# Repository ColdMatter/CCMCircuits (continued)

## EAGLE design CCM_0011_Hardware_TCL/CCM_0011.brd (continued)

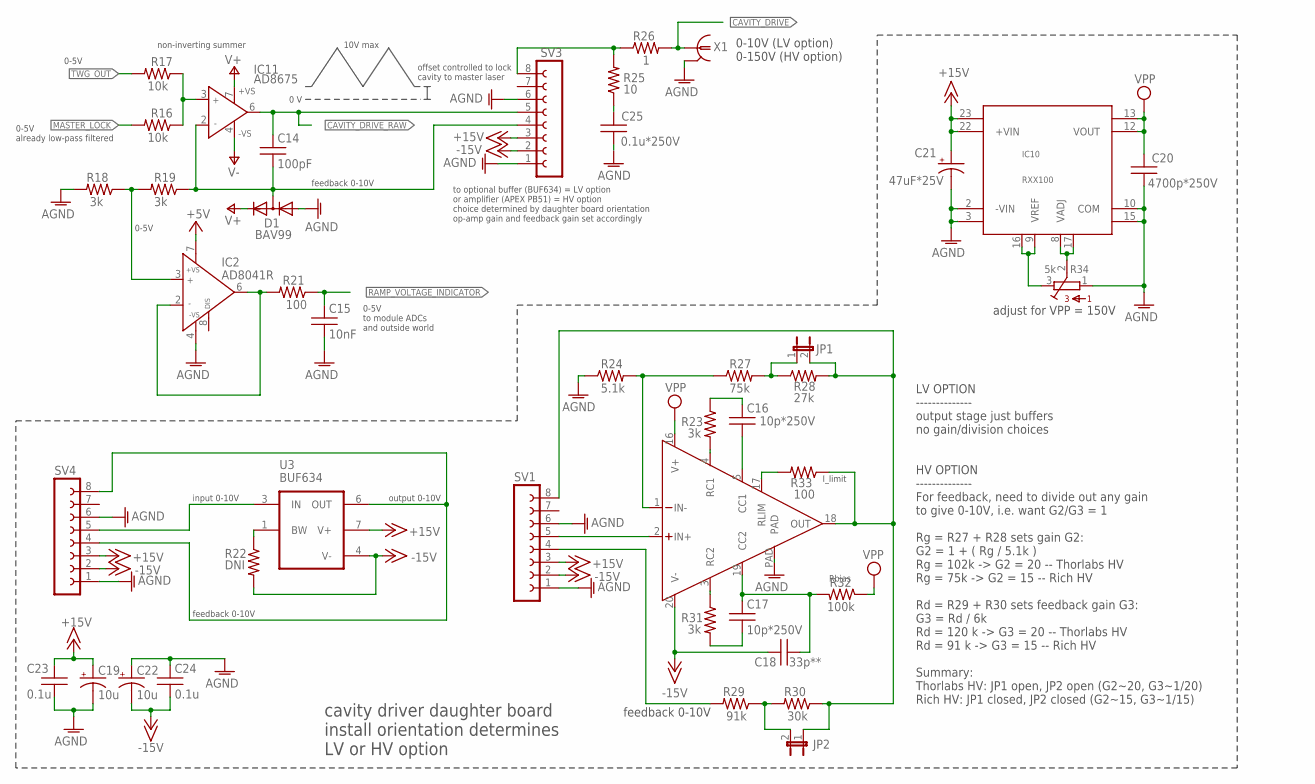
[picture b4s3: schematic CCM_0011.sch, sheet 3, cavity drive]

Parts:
C14: 100pF; 0603
C15: 10nF; 0603
C16, C17: 10p*250V; 0603
C18: 33p**; 0603
C19, C22: 10u; EIA3216
C20: 4700p*250V; 1210
C21: 47uF*25V; EIA7343
C23, C24: 0.1u; 0603
C25: 0.1u*250V; 1210
D1: BAV99; SOT23
IC2: AD8041R; SO8
IC10: RXX100; RXXDIP
IC11: AD8675; SO08
JP1, JP2: JP1E; JP1
R16, R17: 10k; 0603
R18, R19, R23, R31: 3k; 0603
R21, R33: 100; 0603
R22: DNI; 0603
R24: 5.1k; 0603
R25: 10; 2512
R26: 1; 2512
R27: 75k; 0603
R28: 27k; 0603
R29: 91k; 0603
R30: 30k; 0603
R32: 100k; 0603
R34: 5k; 3386H
SV1, SV4: FE08W
SV3: FE08-1; FE08
U3: BUF634; SO8
U$1: PA78; PSOP-20
X1: 1-227161-0; AMP_227161

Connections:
+5V: IC2.7 (+VS); also elsewhere on the board
+15V: C19.A (+), C21.A (+), C23.1, IC10.22 (+VIN), IC10.23 (VIN2+), SV1.3, SV3.3, SV4.3, U3.7 (V+)
-15V: C18.2, C22.C (-), C24.2, R22.2, SV1.2, SV3.2, SV4.2, U3.4 (V-), U$1.20 (V-)
AGND: C15.2, C19.C (-), C20.2, C21.C (-), C22.A (+), C23.2, C24.1, C25.2, D1.1 (A), IC2.4 (-VS), IC10.2 (-VIN), IC10.3 (VIN2-), IC10.10 (COM), IC10.15 (COM2), R18.2, R24.1, R34.1, SV1.1, SV1.6, SV3.1, SV3.6, SV4.1, SV4.6, U$1.PAD, X1.2; also elsewhere on the board
CAVITY_DRIVE: R26.2, X1.1
CAVITY_DRIVE_RAW: C14.1, IC11.6 (OUT), SV3.5
MASTER_LOCK: R16.2
unnamed: SV4.5, U3.3 (IN)
unnamed: IC2.3 (IN+), R18.1, R19.2
unnamed: JP2.2, R29.1, R30.2
unnamed: C14.2, D1.3 (AC), IC11.2 (IN-), R19.1, SV3.4
unnamed: IC11.3 (IN+), R16.1, R17.1
unnamed: R22.1, U3.1 (BW)
unnamed: SV4.4, SV4.8, U3.6 (OUT)
unnamed: SV1.5, U$1.2 (IN+)
unnamed: IC2.2 (IN-), IC2.6 (OUT), R21.2
unnamed: C16.1, R23.1
unnamed: JP1.2, JP2.1, R28.2, R30.1, R33.1, SV1.8, U$1.18 (OUT)
unnamed: R25.2, R26.1, SV3.8
unnamed: C25.1, R25.1
unnamed: R33.2, U$1.17 (RLIM)
unnamed: JP1.1, R27.2, R28.1
unnamed: R23.2, U$1.4 (RC1)
unnamed: R24.2, R27.1, U$1.1 (IN-)
unnamed: C16.2, U$1.5 (CC1)
unnamed: R29.2, SV1.4
unnamed: R31.1, U$1.3 (RC2)
unnamed: C17.1, C18.1, R32.2, U$1.19 (CC2)
unnamed: C17.2, R31.2
unnamed: IC10.9 (VREF), IC10.16 (VREF2), R34.3
unnamed: IC10.8 (VADJ), IC10.17 (VADJ2), R34.2
RAMP_VOLTAGE_INDICATOR: C15.1, R21.1
TWG_OUT: R17.2; also elsewhere on the board
V+: D1.2 (C), IC11.7 (+VS); also elsewhere on the board
V-: IC11.4 (-VS); also elsewhere on the board
VOUT2: C20.1, IC10.12 (VOUT), IC10.13 (VOUT2)
VPP: R32.1, U$1.16 (V+)

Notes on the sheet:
0-5V already low-pass filtered
0-5V
0 V
10V max
offset controlled to lock cavity to master laser
non-inverting summer
feedback 0-10V
0-5V to module ADCs and outside world
to optional buffer (BUF634) = LV option or amplifier (APEX PB51) = HV option choice determined by daughter board orientation op-amp gain and feedback gain set accordingly
output 0-10V
input 0-10V
cavity driver daughter board install orientation determines LV or HV option
LV OPTION -------------- output stage just buffers no gain/division choices HV OPTION -------------- For feedback, need to divide out any gain to give 0-10V, i.e. want G2/G3 = 1 Rg = R27 + R28 sets gain G2: G2 = 1 + ( Rg / 5.1k ) Rg = 102k -> G2 = 20 -- Thorlabs HV Rg = 75k -> G2 = 15 -- Rich HV Rd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
0-10V (LV option) 0-150V (HV option)
Rbias
I_limit
adjust for VPP = 150V

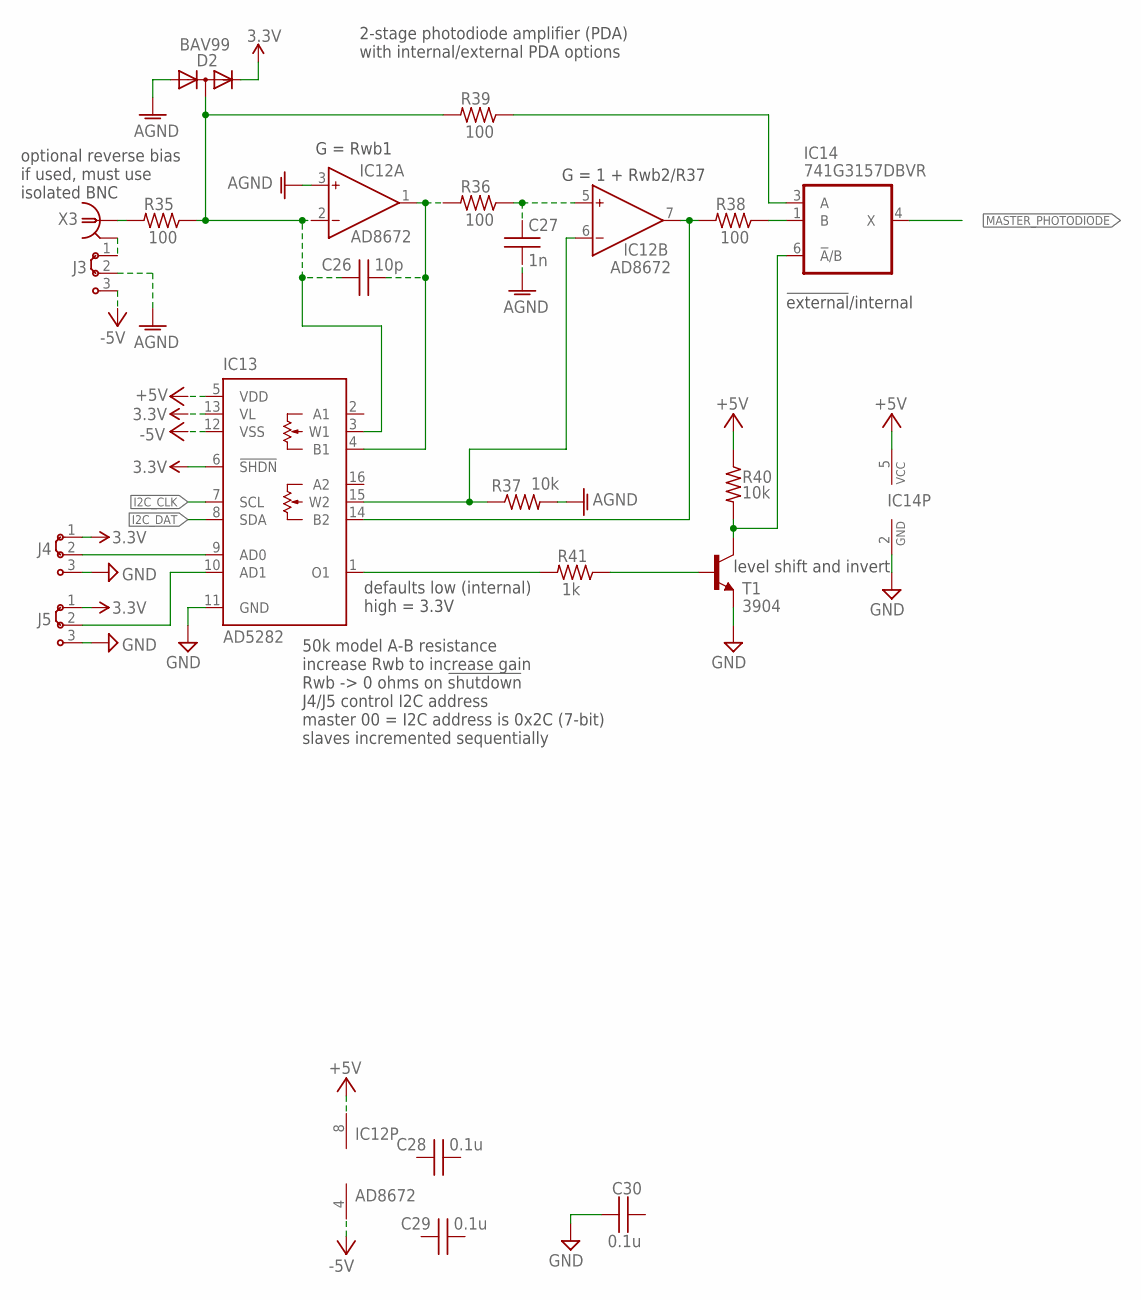
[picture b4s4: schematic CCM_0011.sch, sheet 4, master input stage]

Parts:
C26: 10p; 0603
C27: 1n; 0603
C28, C29, C30: 0.1u; 0603
D2: BAV99; SOT23
IC12: AD8672; SO8
IC13: AD5282; TSSOP16
IC14: 741G3157DBVR; DBV_R-PDSO-G6
J3, J4, J5: J2X2MM; 04C
R35, R36, R38, R39: 100; 0603
R37, R40: 10k; 0603
R41: 1k; 0603
T1: 3904; SOT23-BEC
X3: 1-227161-0; AMP_227161

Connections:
3.3V: D2.2 (C), IC13.6 (!SHDN), IC13.13 (VL), J4.1, J5.1; also elsewhere on the board
+5V: IC12.8 (V+), IC13.5 (VDD), IC14.5 (VCC), R40.1; also elsewhere on the board
-5V: IC12.4 (V-), IC13.12 (VSS), J3.3
AGND: C27.2, D2.1 (A), IC12.3 (IN+), J3.2, R37.2; also elsewhere on the board
GND: C30.2, IC13.11 (GND), IC14.2 (GND), J4.3, J5.3, T1.E; also elsewhere on the board
I2C_CLK: IC13.7 (SCL)
I2C_DAT: IC13.8 (SDA)
MASTER_PHOTODIODE: IC14.4 (X)
unnamed: IC12.7 (OUT), IC13.14 (B2), R38.2
unnamed: J3.1, X3.2
unnamed: C26.1, D2.3 (AC), IC12.2 (IN-), IC13.3 (W1), R35.1, R39.2
unnamed: IC12.6 (IN-), IC13.15 (W2), R37.1
unnamed: R41.1, T1.B
unnamed: IC14.1 (B), R38.1
unnamed: C27.1, IC12.5 (IN+), R36.1
unnamed: C26.2, IC12.1 (OUT), IC13.4 (B1), R36.2
unnamed: IC14.3 (A), R39.1
unnamed: IC14.6 (!A!/B), R40.2, T1.C
unnamed: IC13.1 (O1), R41.2
unnamed: R35.2, X3.1
unnamed: IC13.10 (AD1), J5.2
unnamed: IC13.9 (AD0), J4.2

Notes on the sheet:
optional reverse bias if used, must use isolated BNC
2-stage photodiode amplifier (PDA) with internal/external PDA options
50k model A-B resistance increase Rwb to increase gain Rwb -> 0 ohms on !shutdown! J4/J5 control I2C address master 00 = I2C address is 0x2C (7-bit) slaves incremented sequentially
!external!/internal
defaults low (internal) high = 3.3V
level shift and invert
G = 1 + Rwb2/R37
G = Rwb1

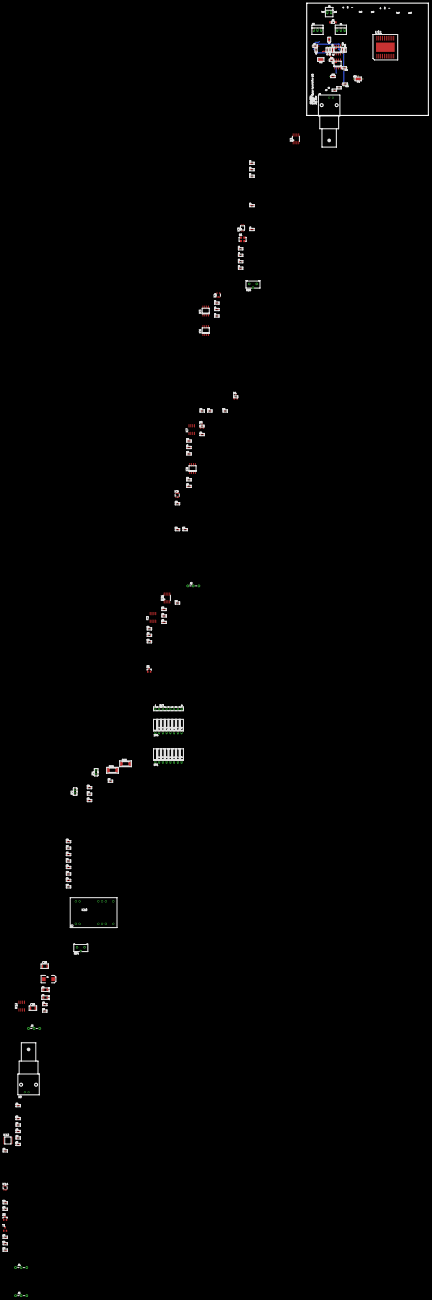
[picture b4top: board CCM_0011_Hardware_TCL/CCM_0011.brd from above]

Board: 2 copper layers, 82.5 x 76.2 mm, 120 parts (0 on the bottom side), 73 nets.

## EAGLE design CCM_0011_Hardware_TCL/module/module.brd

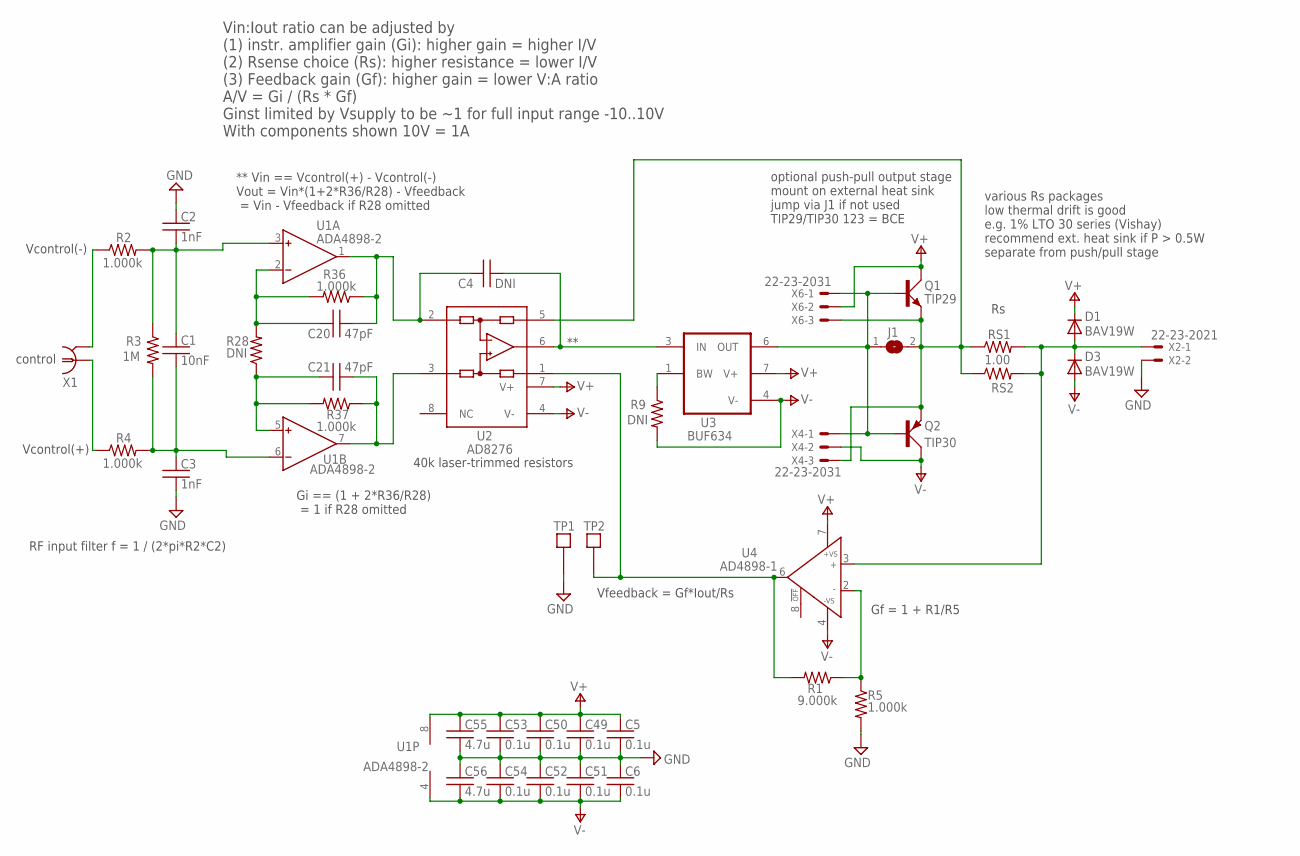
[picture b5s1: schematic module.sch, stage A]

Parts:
C1: 10nF; 0603
C2, C3: 1nF; 0603
C4: DNI; 0603
C5, C6, C49, C50, C51, C52, C53, C54: 0.1u; 0603
C20, C21: 47pF; 0603
C55, C56: 4.7u; 0603
D1, D3: BAV19W; SOD123
J1: SJ
Q1: TIP29; TO220AV
Q2: TIP30; TO220AV
R1: 9.000k; 0603
R2, R4, R5, R36, R37: 1.000k; 0603
R3: 1M; 0603
R9, R28: DNI; 0603
RS1: 1.00; LTO30
RS2: DNI; 2512
TP1, TP2: TESTPOINT
U1: ADA4898-2; SO8
U2: AD8276; SO8
U3: BUF634; SO8
U4: AD4898-1; SO8
X1: 1-227161-0; AMP_227161
X2: 22-23-2021
X4, X6: 22-23-2031

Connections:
GND: C2.1, C3.2, C5.2, C6.1, C49.2, C50.2, C51.1, C52.1, C53.2, C54.1, C55.2, C56.1, R5.2, TP1.P$1, X2.2
unnamed: R2.1, X1.2
unnamed: R4.1, X1.1
unnamed: C4.2, U2.6 (OUT), U3.3 (IN)
unnamed: C1.1, C2.2, R2.2, R3.1, U1.3 (IN+)
unnamed: C1.2, C3.1, R3.2, R4.2, U1.6 (IN-)
unnamed: R1.1, R5.1, U4.2 (IN-)
unnamed: J1.1, Q1.B, Q2.B, U3.6 (OUT), X4.1, X6.1
unnamed: D1.A, D3.C, RS1.P$2 (2), RS2.2, U4.3 (IN+), X2.1
unnamed: J1.2, Q1.E, Q2.E, RS1.P$1 (1), RS2.1, U2.5 (SENSE), X4.3, X6.3
unnamed: R9.1, U3.1 (BW)
unnamed: R1.2, TP2.P$1, U2.1 (REF), U4.6 (OUT)
unnamed: C20.1, R28.2, R36.2, U1.2 (IN-)
unnamed: C21.1, R28.1, R37.2, U1.5 (IN+)
unnamed: C21.2, R37.1, U1.7 (OUT), U2.3 (+IN)
unnamed: C4.1, C20.2, R36.1, U1.1 (OUT), U2.2 (-IN)
V+: C5.1, C49.1, C50.1, C53.1, C55.1, D1.C, Q1.C, U1.8 (V+), U2.7 (V+), U3.7 (V+), U4.7 (+VS), X6.2
V-: C6.2, C51.2, C52.2, C54.2, C56.2, D3.A, Q2.C, R9.2, U1.4 (V-), U2.4 (V-), U3.4 (V-), U4.4 (-VS), X4.2

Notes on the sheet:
control
RF input filter f = 1 / (2*pi*R2*C2)
optional push-pull output stage mount on external heat sink jump via J1 if not used TIP29/TIP30 123 = BCE
40k laser-trimmed resistors
Vcontrol(+)
Vcontrol(-)
various Rs packages low thermal drift is good e.g. 1% LTO 30 series (Vishay) recommend ext. heat sink if P > 0.5W separate from push/pull stage
** Vin == Vcontrol(+) - Vcontrol(-) Vout = Vin*(1+2*R36/R28) - Vfeedback = Vin - Vfeedback if R28 omitted
Gi == (1 + 2*R36/R28) = 1 if R28 omitted
Vfeedback = Gf*Iout/Rs
Gf = 1 + R1/R5
Vin:Iout ratio can be adjusted by (1) instr. amplifier gain (Gi): higher gain = higher I/V (2) Rsense choice (Rs): higher resistance = lower I/V (3) Feedback gain (Gf): higher gain = lower V:A ratio A/V = Gi / (Rs * Gf) Ginst limited by Vsupply to be ~1 for full input range -10..10V With components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

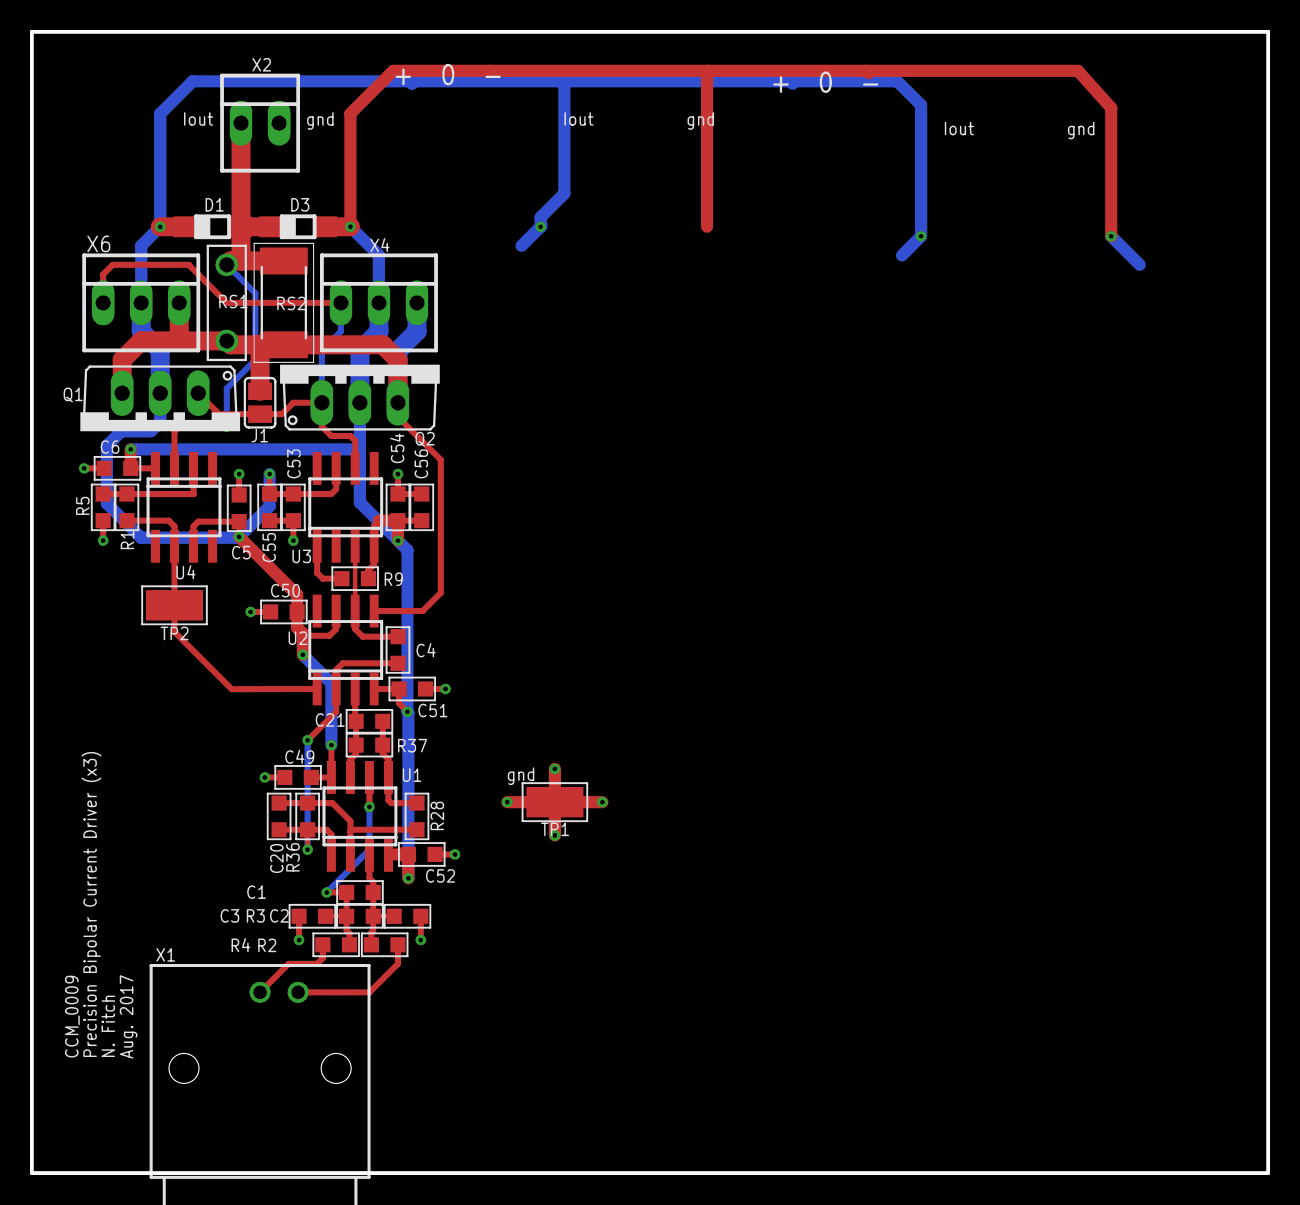
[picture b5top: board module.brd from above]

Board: 2 copper layers, 82.5 x 76.2 mm, 42 parts (0 on the bottom side), 18 nets.

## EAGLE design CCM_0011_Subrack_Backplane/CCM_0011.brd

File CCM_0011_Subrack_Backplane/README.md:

Subrack Backplane
===========
     
This circuit is an attempt to create a subrack standard for CCM circuits.  It uses a 64-pin bus based on the EURO-card standard (100 mm tall boards x various lengths, typically 160 mm) using DIN41612 "Type B" connectors.  The bus provides separate analog and digital ground planes and associated power supplies of +/-15V and +/-5V, respectively.  The backplane provides female connectors with a 4HP pitch.

We have a number of existing circuits that use a 32-pin rear connector (actually a 64-pin connector with half of the pins unpopulated).  The bus standard defined here should be compatible with our existing circuits.

In addition to power rails, the backplane also provides various communication buses, which can be used with microcontroller projects.  Take care though, the GPIOX and ANX lines are shared across all daughter boards, which can cause conflicts if you aren't careful.  In a similar vein, please only install a single power-supply module!

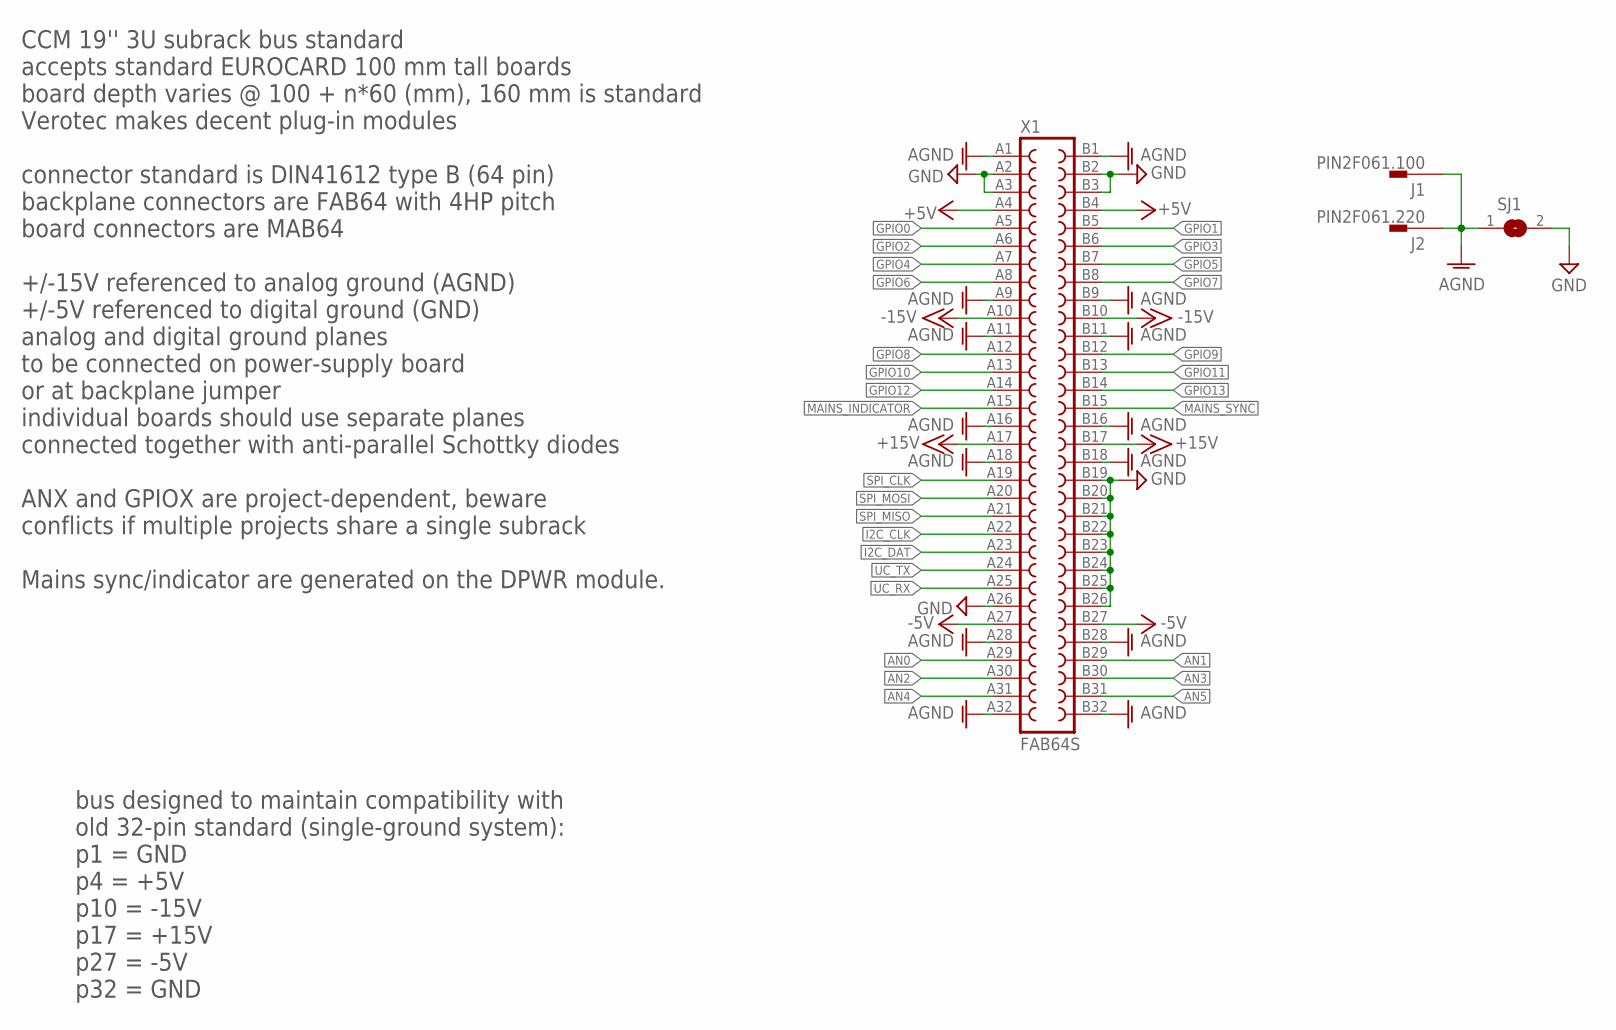
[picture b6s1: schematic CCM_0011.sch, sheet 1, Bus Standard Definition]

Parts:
J1: PIN2F061.100; F061.100
J2: PIN2F061.220; F061.220
SJ1: SJ
X1: FAB64S

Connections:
+5V: X1.A4, X1.B4; also elsewhere on the board
+15V: X1.A17, X1.B17; also elsewhere on the board
-5V: X1.A27, X1.B27; also elsewhere on the board
-15V: X1.A10, X1.B10; also elsewhere on the board
AGND: J1.A1, J1.A2, J2.1A, J2.1B, SJ1.1, X1.A1, X1.A9, X1.A11, X1.A16, X1.A18, X1.A28, X1.A32, X1.B1, X1.B9, X1.B11, X1.B16, X1.B18, X1.B28, X1.B32; also elsewhere on the board
AN0: X1.A29; also elsewhere on the board
AN1: X1.B29; also elsewhere on the board
AN2: X1.A30; also elsewhere on the board
AN3: X1.B30; also elsewhere on the board
AN4: X1.A31; also elsewhere on the board
AN5: X1.B31; also elsewhere on the board
GND: SJ1.2, X1.A2, X1.A3, X1.A26, X1.B2, X1.B3, X1.B19, X1.B20, X1.B21, X1.B22, X1.B23, X1.B24, X1.B25, X1.B26; also elsewhere on the board
GPIO0: X1.A5; also elsewhere on the board
GPIO1: X1.B5; also elsewhere on the board
GPIO2: X1.A6; also elsewhere on the board
GPIO3: X1.B6; also elsewhere on the board
GPIO4: X1.A7; also elsewhere on the board
GPIO5: X1.B7; also elsewhere on the board
GPIO6: X1.A8; also elsewhere on the board
GPIO7: X1.B8; also elsewhere on the board
GPIO8: X1.A12; also elsewhere on the board
GPIO9: X1.B12; also elsewhere on the board
GPIO10: X1.A13; also elsewhere on the board
GPIO11: X1.B13; also elsewhere on the board
GPIO12: X1.A14; also elsewhere on the board
GPIO13: X1.B14; also elsewhere on the board
I2C_CLK: X1.A22; also elsewhere on the board
I2C_DAT: X1.A23; also elsewhere on the board
MAINS_INDICATOR: X1.A15
MAINS_SYNC: X1.B15
SPI_CLK: X1.A19; also elsewhere on the board
SPI_MISO: X1.A21; also elsewhere on the board
SPI_MOSI: X1.A20; also elsewhere on the board
UC_RX: X1.A25; also elsewhere on the board
UC_TX: X1.A24; also elsewhere on the board

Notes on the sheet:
bus designed to maintain compatibility with old 32-pin standard (single-ground system): p1 = GND p4 = +5V p10 = -15V p17 = +15V p27 = -5V p32 = GND
CCM 19'' 3U subrack bus standard accepts standard EUROCARD 100 mm tall boards board depth varies @ 100 + n*60 (mm), 160 mm is standard Verotec makes decent plug-in modules connector standard is DIN41612 type B (64 pin) backplane connectors are FAB64 with 4HP pitch board connectors are MAB64 +/-15V 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

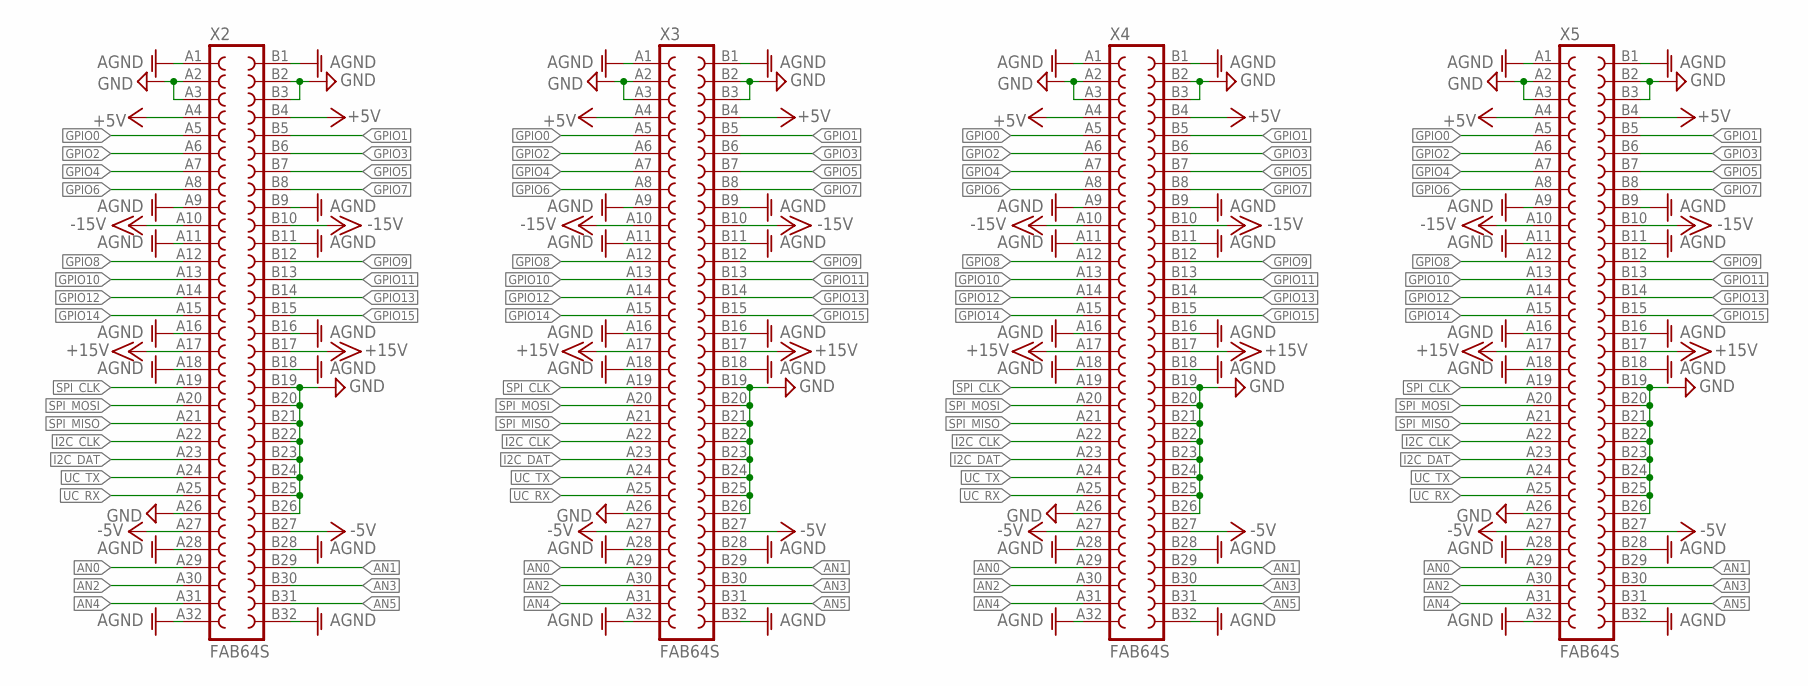
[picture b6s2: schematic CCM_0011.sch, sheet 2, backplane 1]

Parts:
X2, X3, X4, X5: FAB64S

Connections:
+5V: X2.A4, X2.B4, X3.A4, X3.B4, X4.A4, X4.B4, X5.A4, X5.B4; also elsewhere on the board
+15V: X2.A17, X2.B17, X3.A17, X3.B17, X4.A17, X4.B17, X5.A17, X5.B17; also elsewhere on the board
-5V: X2.A27, X2.B27, X3.A27, X3.B27, X4.A27, X4.B27, X5.A27, X5.B27; also elsewhere on the board
-15V: X2.A10, X2.B10, X3.A10, X3.B10, X4.A10, X4.B10, X5.A10, X5.B10; also elsewhere on the board
AGND: X2.A1, X2.A9, X2.A11, X2.A16, X2.A18, X2.A28, X2.A32, X2.B1, X2.B9, X2.B11, X2.B16, X2.B18, X2.B28, X2.B32, X3.A1, X3.A9, X3.A11, X3.A16, X3.A18, X3.A28, X3.A32, X3.B1, X3.B9, X3.B11, X3.B16, X3.B18, X3.B28, X3.B32, X4.A1, X4.A9, X4.A11, X4.A16, X4.A18, X4.A28, X4.A32, X4.B1, X4.B9, X4.B11, X4.B16, X4.B18, X4.B28, X4.B32, X5.A1, X5.A9, X5.A11, X5.A16, X5.A18, X5.A28, X5.A32, X5.B1, X5.B9, X5.B11, X5.B16, X5.B18, X5.B28, X5.B32; also elsewhere on the board
AN0: X2.A29, X3.A29, X4.A29, X5.A29; also elsewhere on the board
AN1: X2.B29, X3.B29, X4.B29, X5.B29; also elsewhere on the board
AN2: X2.A30, X3.A30, X4.A30, X5.A30; also elsewhere on the board
AN3: X2.B30, X3.B30, X4.B30, X5.B30; also elsewhere on the board
AN4: X2.A31, X3.A31, X4.A31, X5.A31; also elsewhere on the board
AN5: X2.B31, X3.B31, X4.B31, X5.B31; also elsewhere on the board
GND: X2.A2, X2.A3, X2.A26, X2.B2, X2.B3, X2.B19, X2.B20, X2.B21, X2.B22, X2.B23, X2.B24, X2.B25, X2.B26, X3.A2, X3.A3, X3.A26, X3.B2, X3.B3, X3.B19, X3.B20, X3.B21, X3.B22, X3.B23, X3.B24, X3.B25, X3.B26, X4.A2, X4.A3, X4.A26, X4.B2, X4.B3, X4.B19, X4.B20, X4.B21, X4.B22, X4.B23, X4.B24, X4.B25, X4.B26, X5.A2, X5.A3, X5.A26, X5.B2, X5.B3, X5.B19, X5.B20, X5.B21, X5.B22, X5.B23, X5.B24, X5.B25, X5.B26; also elsewhere on the board
GPIO0: X2.A5, X3.A5, X4.A5, X5.A5; also elsewhere on the board
GPIO1: X2.B5, X3.B5, X4.B5, X5.B5; also elsewhere on the board
GPIO2: X2.A6, X3.A6, X4.A6, X5.A6; also elsewhere on the board
GPIO3: X2.B6, X3.B6, X4.B6, X5.B6; also elsewhere on the board
GPIO4: X2.A7, X3.A7, X4.A7, X5.A7; also elsewhere on the board
GPIO5: X2.B7, X3.B7, X4.B7, X5.B7; also elsewhere on the board
GPIO6: X2.A8, X3.A8, X4.A8, X5.A8; also elsewhere on the board
GPIO7: X2.B8, X3.B8, X4.B8, X5.B8; also elsewhere on the board
GPIO8: X2.A12, X3.A12, X4.A12, X5.A12; also elsewhere on the board
GPIO9: X2.B12, X3.B12, X4.B12, X5.B12; also elsewhere on the board
GPIO10: X2.A13, X3.A13, X4.A13, X5.A13; also elsewhere on the board
GPIO11: X2.B13, X3.B13, X4.B13, X5.B13; also elsewhere on the board
GPIO12: X2.A14, X3.A14, X4.A14, X5.A14; also elsewhere on the board
GPIO13: X2.B14, X3.B14, X4.B14, X5.B14; also elsewhere on the board
GPIO14: X2.A15, X3.A15, X4.A15, X5.A15; also elsewhere on the board
GPIO15: X2.B15, X3.B15, X4.B15, X5.B15; also elsewhere on the board
I2C_CLK: X2.A22, X3.A22, X4.A22, X5.A22; also elsewhere on the board
I2C_DAT: X2.A23, X3.A23, X4.A23, X5.A23; also elsewhere on the board
SPI_CLK: X2.A19, X3.A19, X4.A19, X5.A19; also elsewhere on the board
SPI_MISO: X2.A21, X3.A21, X4.A21, X5.A21; also elsewhere on the board
SPI_MOSI: X2.A20, X3.A20, X4.A20, X5.A20; also elsewhere on the board
UC_RX: X2.A25, X3.A25, X4.A25, X5.A25; also elsewhere on the board
UC_TX: X2.A24, X3.A24, X4.A24, X5.A24; also elsewhere on the board

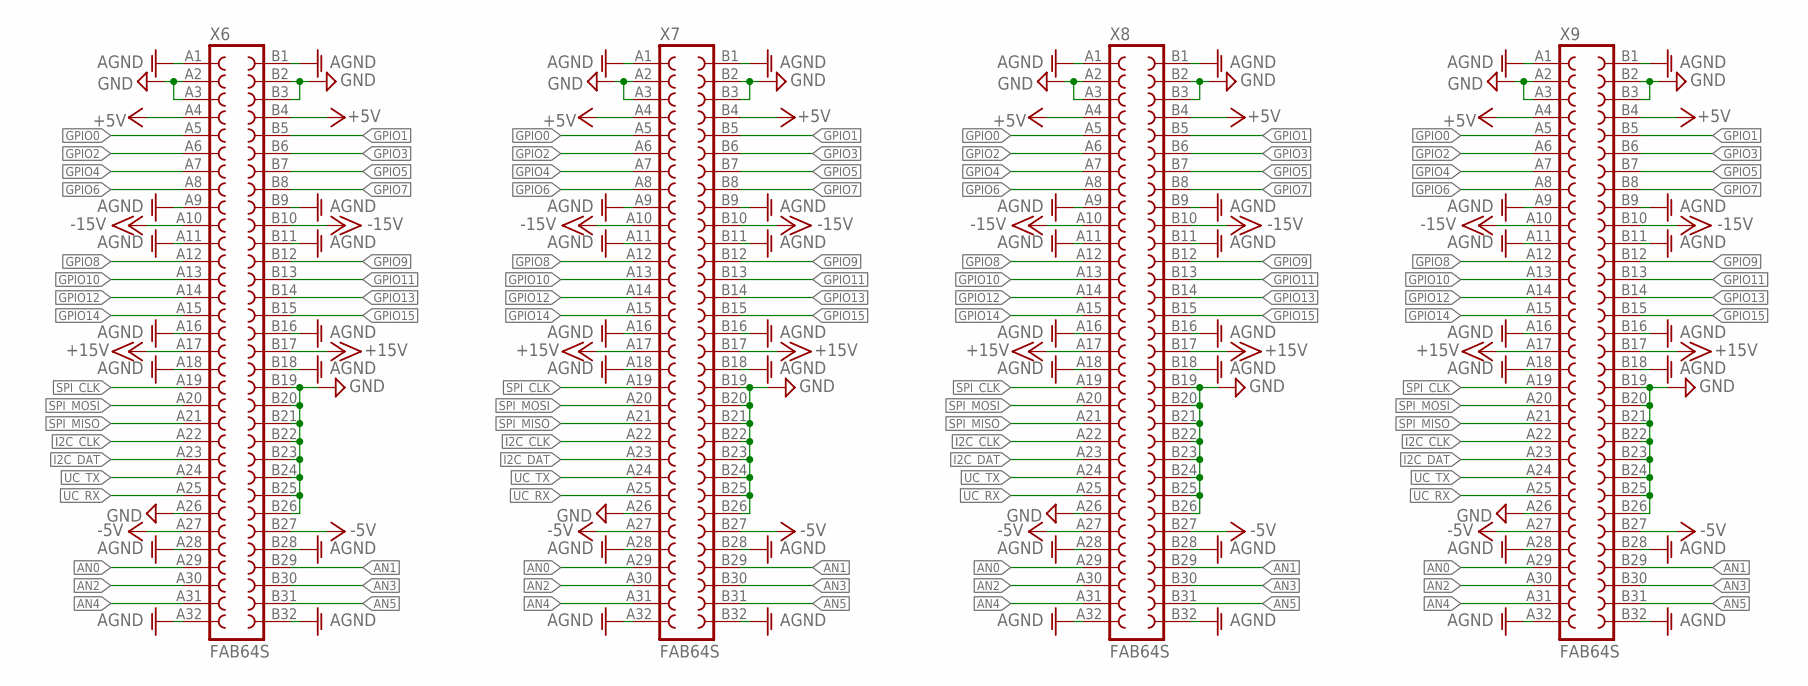
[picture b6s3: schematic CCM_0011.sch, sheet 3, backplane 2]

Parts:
X6, X7, X8, X9: FAB64S

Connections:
+5V: X6.A4, X6.B4, X7.A4, X7.B4, X8.A4, X8.B4, X9.A4, X9.B4; also elsewhere on the board
+15V: X6.A17, X6.B17, X7.A17, X7.B17, X8.A17, X8.B17, X9.A17, X9.B17; also elsewhere on the board
-5V: X6.A27, X6.B27, X7.A27, X7.B27, X8.A27, X8.B27, X9.A27, X9.B27; also elsewhere on the board
-15V: X6.A10, X6.B10, X7.A10, X7.B10, X8.A10, X8.B10, X9.A10, X9.B10; also elsewhere on the board
AGND: X6.A1, X6.A9, X6.A11, X6.A16, X6.A18, X6.A28, X6.A32, X6.B1, X6.B9, X6.B11, X6.B16, X6.B18, X6.B28, X6.B32, X7.A1, X7.A9, X7.A11, X7.A16, X7.A18, X7.A28, X7.A32, X7.B1, X7.B9, X7.B11, X7.B16, X7.B18, X7.B28, X7.B32, X8.A1, X8.A9, X8.A11, X8.A16, X8.A18, X8.A28, X8.A32, X8.B1, X8.B9, X8.B11, X8.B16, X8.B18, X8.B28, X8.B32, X9.A1, X9.A9, X9.A11, X9.A16, X9.A18, X9.A28, X9.A32, X9.B1, X9.B9, X9.B11, X9.B16, X9.B18, X9.B28, X9.B32; also elsewhere on the board
AN0: X6.A29, X7.A29, X8.A29, X9.A29; also elsewhere on the board
AN1: X6.B29, X7.B29, X8.B29, X9.B29; also elsewhere on the board
AN2: X6.A30, X7.A30, X8.A30, X9.A30; also elsewhere on the board
AN3: X6.B30, X7.B30, X8.B30, X9.B30; also elsewhere on the board
AN4: X6.A31, X7.A31, X8.A31, X9.A31; also elsewhere on the board
AN5: X6.B31, X7.B31, X8.B31, X9.B31; also elsewhere on the board
GND: X6.A2, X6.A3, X6.A26, X6.B2, X6.B3, X6.B19, X6.B20, X6.B21, X6.B22, X6.B23, X6.B24, X6.B25, X6.B26, X7.A2, X7.A3, X7.A26, X7.B2, X7.B3, X7.B19, X7.B20, X7.B21, X7.B22, X7.B23, X7.B24, X7.B25, X7.B26, X8.A2, X8.A3, X8.A26, X8.B2, X8.B3, X8.B19, X8.B20, X8.B21, X8.B22, X8.B23, X8.B24, X8.B25, X8.B26, X9.A2, X9.A3, X9.A26, X9.B2, X9.B3, X9.B19, X9.B20, X9.B21, X9.B22, X9.B23, X9.B24, X9.B25, X9.B26; also elsewhere on the board
GPIO0: X6.A5, X7.A5, X8.A5, X9.A5; also elsewhere on the board
GPIO1: X6.B5, X7.B5, X8.B5, X9.B5; also elsewhere on the board
GPIO2: X6.A6, X7.A6, X8.A6, X9.A6; also elsewhere on the board
GPIO3: X6.B6, X7.B6, X8.B6, X9.B6; also elsewhere on the board
GPIO4: X6.A7, X7.A7, X8.A7, X9.A7; also elsewhere on the board
GPIO5: X6.B7, X7.B7, X8.B7, X9.B7; also elsewhere on the board
GPIO6: X6.A8, X7.A8, X8.A8, X9.A8; also elsewhere on the board
GPIO7: X6.B8, X7.B8, X8.B8, X9.B8; also elsewhere on the board
GPIO8: X6.A12, X7.A12, X8.A12, X9.A12; also elsewhere on the board
GPIO9: X6.B12, X7.B12, X8.B12, X9.B12; also elsewhere on the board
GPIO10: X6.A13, X7.A13, X8.A13, X9.A13; also elsewhere on the board
GPIO11: X6.B13, X7.B13, X8.B13, X9.B13; also elsewhere on the board
GPIO12: X6.A14, X7.A14, X8.A14, X9.A14; also elsewhere on the board
GPIO13: X6.B14, X7.B14, X8.B14, X9.B14; also elsewhere on the board
GPIO14: X6.A15, X7.A15, X8.A15, X9.A15; also elsewhere on the board
GPIO15: X6.B15, X7.B15, X8.B15, X9.B15; also elsewhere on the board
I2C_CLK: X6.A22, X7.A22, X8.A22, X9.A22; also elsewhere on the board
I2C_DAT: X6.A23, X7.A23, X8.A23, X9.A23; also elsewhere on the board
SPI_CLK: X6.A19, X7.A19, X8.A19, X9.A19; also elsewhere on the board
SPI_MISO: X6.A21, X7.A21, X8.A21, X9.A21; also elsewhere on the board
SPI_MOSI: X6.A20, X7.A20, X8.A20, X9.A20; also elsewhere on the board
UC_RX: X6.A25, X7.A25, X8.A25, X9.A25; also elsewhere on the board
UC_TX: X6.A24, X7.A24, X8.A24, X9.A24; also elsewhere on the board

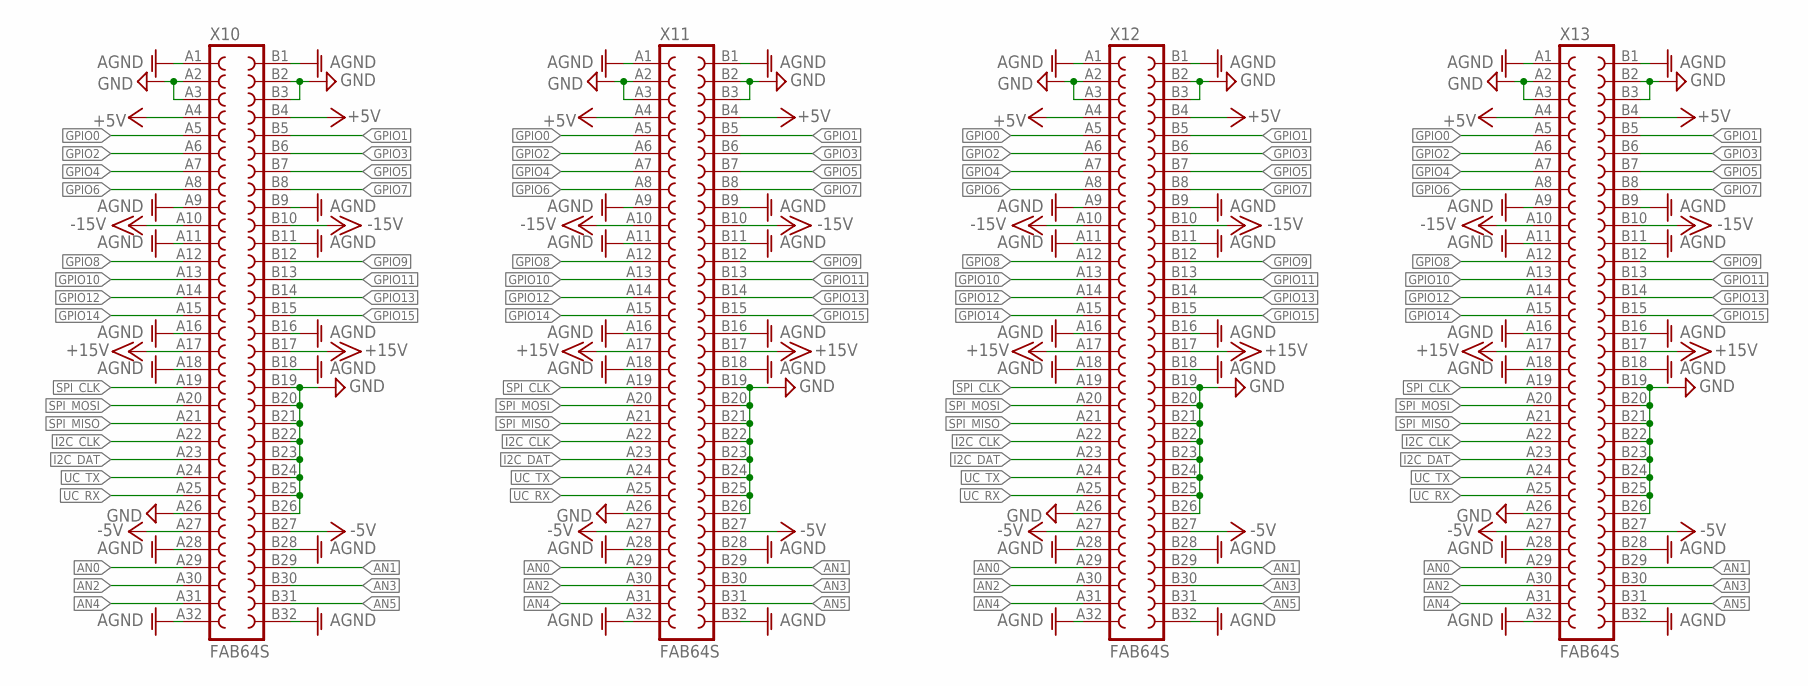
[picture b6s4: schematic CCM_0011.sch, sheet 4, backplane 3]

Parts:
X10, X11, X12, X13: FAB64S

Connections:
+5V: X10.A4, X10.B4, X11.A4, X11.B4, X12.A4, X12.B4, X13.A4, X13.B4; also elsewhere on the board
+15V: X10.A17, X10.B17, X11.A17, X11.B17, X12.A17, X12.B17, X13.A17, X13.B17; also elsewhere on the board
-5V: X10.A27, X10.B27, X11.A27, X11.B27, X12.A27, X12.B27, X13.A27, X13.B27; also elsewhere on the board
-15V: X10.A10, X10.B10, X11.A10, X11.B10, X12.A10, X12.B10, X13.A10, X13.B10; also elsewhere on the board
AGND: X10.A1, X10.A9, X10.A11, X10.A16, X10.A18, X10.A28, X10.A32, X10.B1, X10.B9, X10.B11, X10.B16, X10.B18, X10.B28, X10.B32, X11.A1, X11.A9, X11.A11, X11.A16, X11.A18, X11.A28, X11.A32, X11.B1, X11.B9, X11.B11, X11.B16, X11.B18, X11.B28, X11.B32, X12.A1, X12.A9, X12.A11, X12.A16, X12.A18, X12.A28, X12.A32, X12.B1, X12.B9, X12.B11, X12.B16, X12.B18, X12.B28, X12.B32, X13.A1, X13.A9, X13.A11, X13.A16, X13.A18, X13.A28, X13.A32, X13.B1, X13.B9, X13.B11, X13.B16, X13.B18, X13.B28, X13.B32; also elsewhere on the board
AN0: X10.A29, X11.A29, X12.A29, X13.A29; also elsewhere on the board
AN1: X10.B29, X11.B29, X12.B29, X13.B29; also elsewhere on the board
AN2: X10.A30, X11.A30, X12.A30, X13.A30; also elsewhere on the board
AN3: X10.B30, X11.B30, X12.B30, X13.B30; also elsewhere on the board
AN4: X10.A31, X11.A31, X12.A31, X13.A31; also elsewhere on the board
AN5: X10.B31, X11.B31, X12.B31, X13.B31; also elsewhere on the board
GND: X10.A2, X10.A3, X10.A26, X10.B2, X10.B3, X10.B19, X10.B20, X10.B21, X10.B22, X10.B23, X10.B24, X10.B25, X10.B26, X11.A2, X11.A3, X11.A26, X11.B2, X11.B3, X11.B19, X11.B20, X11.B21, X11.B22, X11.B23, X11.B24, X11.B25, X11.B26, X12.A2, X12.A3, X12.A26, X12.B2, X12.B3, X12.B19, X12.B20, X12.B21, X12.B22, X12.B23, X12.B24, X12.B25, X12.B26, X13.A2, X13.A3, X13.A26, X13.B2, X13.B3, X13.B19, X13.B20, X13.B21, X13.B22, X13.B23, X13.B24, X13.B25, X13.B26; also elsewhere on the board
GPIO0: X10.A5, X11.A5, X12.A5, X13.A5; also elsewhere on the board
GPIO1: X10.B5, X11.B5, X12.B5, X13.B5; also elsewhere on the board
GPIO2: X10.A6, X11.A6, X12.A6, X13.A6; also elsewhere on the board
GPIO3: X10.B6, X11.B6, X12.B6, X13.B6; also elsewhere on the board
GPIO4: X10.A7, X11.A7, X12.A7, X13.A7; also elsewhere on the board
GPIO5: X10.B7, X11.B7, X12.B7, X13.B7; also elsewhere on the board
GPIO6: X10.A8, X11.A8, X12.A8, X13.A8; also elsewhere on the board
GPIO7: X10.B8, X11.B8, X12.B8, X13.B8; also elsewhere on the board
GPIO8: X10.A12, X11.A12, X12.A12, X13.A12; also elsewhere on the board
GPIO9: X10.B12, X11.B12, X12.B12, X13.B12; also elsewhere on the board
GPIO10: X10.A13, X11.A13, X12.A13, X13.A13; also elsewhere on the board
GPIO11: X10.B13, X11.B13, X12.B13, X13.B13; also elsewhere on the board
GPIO12: X10.A14, X11.A14, X12.A14, X13.A14; also elsewhere on the board
GPIO13: X10.B14, X11.B14, X12.B14, X13.B14; also elsewhere on the board
GPIO14: X10.A15, X11.A15, X12.A15, X13.A15; also elsewhere on the board
GPIO15: X10.B15, X11.B15, X12.B15, X13.B15; also elsewhere on the board
I2C_CLK: X10.A22, X11.A22, X12.A22, X13.A22; also elsewhere on the board
I2C_DAT: X10.A23, X11.A23, X12.A23, X13.A23; also elsewhere on the board
SPI_CLK: X10.A19, X11.A19, X12.A19, X13.A19; also elsewhere on the board
SPI_MISO: X10.A21, X11.A21, X12.A21, X13.A21; also elsewhere on the board
SPI_MOSI: X10.A20, X11.A20, X12.A20, X13.A20; also elsewhere on the board
UC_RX: X10.A25, X11.A25, X12.A25, X13.A25; also elsewhere on the board
UC_TX: X10.A24, X11.A24, X12.A24, X13.A24; also elsewhere on the board
